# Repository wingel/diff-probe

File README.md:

What is different in this fork?
===============================
* KiCAD version of only the tested B variant
* Board slightly optimized (NF resistors removed)
* JLCPCB production files added (with assembly)

An almost GHZ active differential probe
=======================================

This is the design for an active differential probe which has a
bandwidth of about 800MHz and which is useful to beyond 1GHz.

I have written some articles about the probe:
[Part&nbsp;1](http://blog.weinigel.se/2016/02/26/ghz-differential-probe.html),
[Part&nbsp;2](http://blog.weinigel.se/2016/02/28/ghz-differential-probe-2.html), and
[Part&nbsp;3](http://blog.weinigel.se/2016/03/16/ghz-differential-probe-3.html).

A few notes
===========

So far I have only built the B variant of the probe, that is, the
probe with separate OP amps for the inputs.

On variant B, the input resistors R20/R21, R28/R29 and output
resistors R30/R31 are arranged in such a way that one can use just one
resistor between the input of the first resistor to the output of the
second resistor.  That's why it says "0Ω/NF" on one of the resistors
in both pairs.

The image in [S21ProbeBW_1.png](S21ProbeBW_1.png) shows a plot of the
frequency response for variant B using LMH6702 OP-AMPs, 150Ω on R20
and R28, 220Ω on R26, R27, R37 and R38 and 1.1k on R22 and R32.  Note
that the 150Ω resistors were mounted across R20/R21 and R28/R29 and
the and 50Ω matching resistor for the output was mounted across
R30/R31.  The power supply with a LMH6702 OP-AMPs should be about 5V
and the probe should be able to measure signals up to about +/-3.3V.

If you want the probe input to be AC coupled you can mount the input
resistor in its proper position on R20 and R28 and mount a capacitor
(0.1µF might be a good starting value) on R21 and R29.  You can also
AC couple the output by mounting the 50Ω matching resistor on R30 and
a another small capacitor on R31.

License
=======

[diff-probe](https://github.com/wingel/diff-probe) by
[Christer Weinigel](mailto:christer@weinigel.se) is licensed under a
[Creative Commons Attribution 4.0 International
License](http://creativecommons.org/licenses/by/4.0/).

The intent is to make this PCB available to anyone that finds it
useful as long as I get credit for the original design.  If you want
to use the design and have issues with the above license, please
contact me.

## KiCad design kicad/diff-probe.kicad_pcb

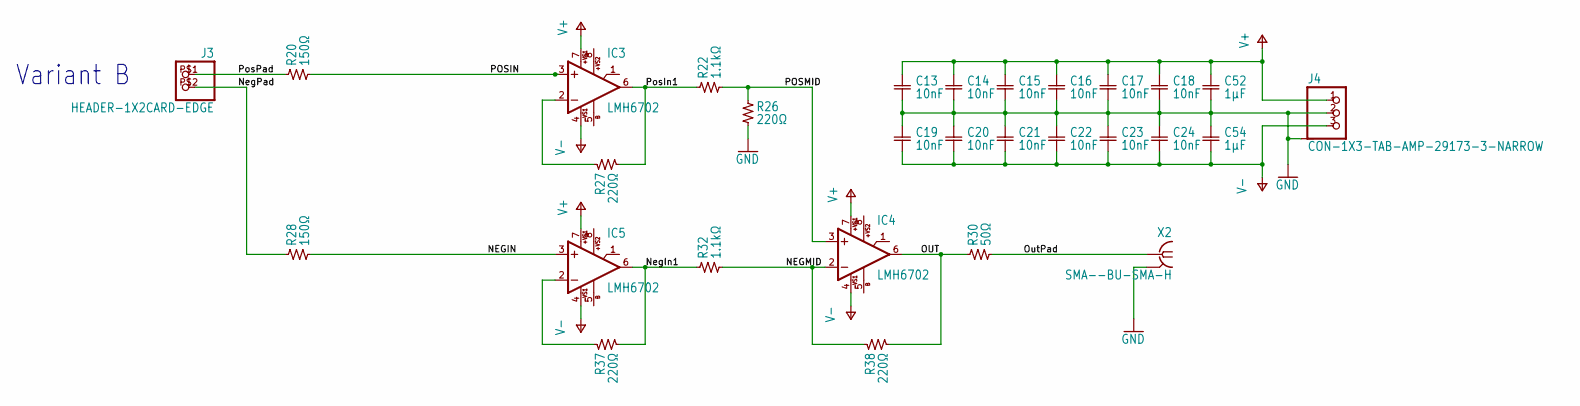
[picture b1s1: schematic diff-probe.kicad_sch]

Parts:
C13, C14, C15, C16, C17, C18, C19, C20, C21, C22, C23, C24: 10nF; 0402-SQUARE; LCSC C15195
C52, C54: 1µF; 0603; LCSC C52923
IC3, IC4, IC5: LMH6702; SO08
J3: HEADER-1X2CARD-EDGE; CARD_EDGE_PADS-1X2
J4: CON-1X3-TAB-AMP-29173-3-NARROW; AMP-29173-3-NARROW
R20, R28: 150Ω; 0402-SQUARE; LCSC C25082
R22, R32: 1.1kΩ; 0402-SQUARE; LCSC C25860
R26, R27, R37, R38: 220Ω; 0402-SQUARE; LCSC C25091
R30: 50Ω; 0402-SQUARE; LCSC C477760
X2: SMA--BU-SMA-H; BU-SMA-H; LCSC C1509230

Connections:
/NEGIN: IC5.3 (+IN), R28.P$2 (2)
/NEGMID: IC4.2 (-IN), R32.P$2 (2), R38.P$1 (1)
/NegIn1: IC5.6 (OUT), R32.P$1 (1), R37.P$2 (2)
/NegPad: J3.P$2 (2), R28.P$1 (1)
/OUT: IC4.6 (OUT), R30.P$1 (1), R38.P$2 (2)
/OutPad: R30.P$2 (2), X2.1
/POSIN: IC3.3 (+IN), R20.P$2 (2)
/POSMID: IC4.3 (+IN), R22.P$2 (2), R26.P$1 (1)
/PosIn1: IC3.6 (OUT), R22.P$1 (1), R27.P$2 (2)
/PosPad: J3.P$1 (1), R20.P$1 (1)
GND: C13.P$2 (2), C14.P$2 (2), C15.P$2 (2), C16.P$2 (2), C17.P$2 (2), C18.P$2 (2), C19.P$1 (1), C20.P$1 (1), C21.P$1 (1), C22.P$1 (1), C23.P$1 (1), C24.P$1 (1), C52.2, C54.1, J4.2, J4.P$4, J4.P$5, R26.P$2 (2), X2.2, X2.3 (2), X2.4 (2), X2.5 (2)
unnamed: IC3.2 (-IN), R27.P$1 (1)
unnamed: IC5.2 (-IN), R37.P$1 (1)
V+: C13.P$1 (1), C14.P$1 (1), C15.P$1 (1), C16.P$1 (1), C17.P$1 (1), C18.P$1 (1), C52.1, IC3.7 (+VS1), IC4.7 (+VS1), IC5.7 (+VS1), J4.1
V-: C19.P$2 (2), C20.P$2 (2), C21.P$2 (2), C22.P$2 (2), C23.P$2 (2), C24.P$2 (2), C54.2, IC3.4 (-VS1), IC4.4 (-VS1), IC5.4 (-VS1), J4.3

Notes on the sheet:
Variant B

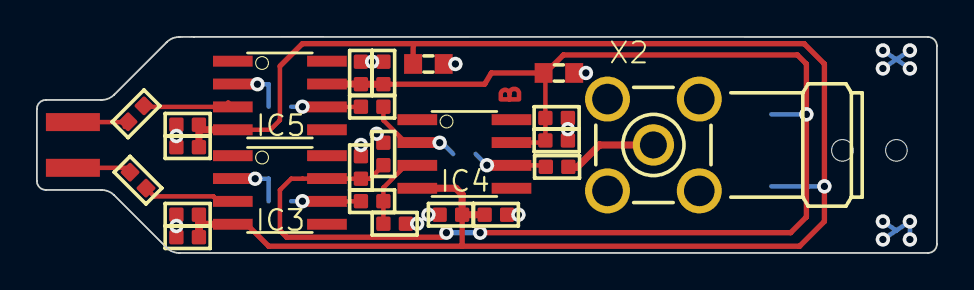
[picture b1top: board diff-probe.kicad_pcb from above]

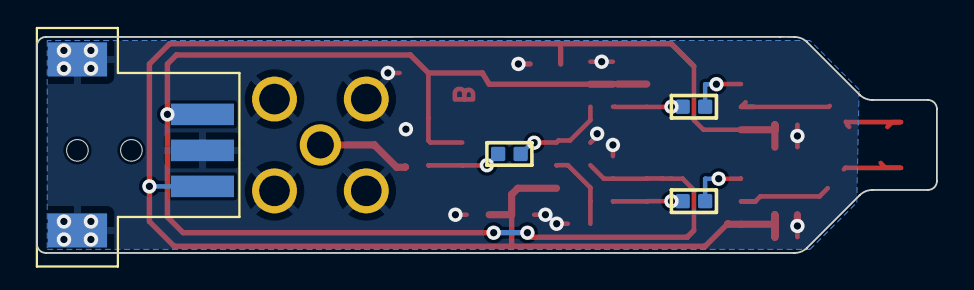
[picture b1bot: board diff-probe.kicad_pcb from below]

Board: 2 copper layers, 50.0 x 12.0 mm, 29 parts (4 on the bottom side), 15 nets.

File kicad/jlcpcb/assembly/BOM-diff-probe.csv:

Comment,Designator,Footprint,LCSC
150Ω,"R20,R28",0402-SQUARE,C25082
10nF,"C13,C14,C15,C16,C17,C18,C19,C20,C21,C22,C23,C24",0402-SQUARE,C15195
220Ω,"R26,R27,R37,R38",0402-SQUARE,C25091
50Ω,R30,0402-SQUARE,C477760
1.1kΩ,"R22,R32",0402-SQUARE,C25860
SMA--BU-SMA-H,X2,BU-SMA-H,C1509230
1µF,"C52,C54",0603,C52923

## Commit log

2016-03-31 Create repository
2016-03-31 Add README.md
2016-03-31 Add plot of probe bandwith
2016-03-31 Add eagle files for diff probe
2017-05-15 Add PDF of schematics
2017-05-15 Add "Variant" text to schematics.
2021-12-08 add basic kicad version
2021-12-08 Remove NF resistors and add LCSC part numbers
2021-12-08 remove NF resistors and rotate input resistors
2021-12-08 use a better SMA connector
2021-12-08 add JLCPCB production files
2021-12-08 fix DRC (edge cuts and closeness of trace to letter)
2021-12-08 tidy schematic
2022-01-15 give nets names to make the PCB more readable
2022-01-15 optimize output
